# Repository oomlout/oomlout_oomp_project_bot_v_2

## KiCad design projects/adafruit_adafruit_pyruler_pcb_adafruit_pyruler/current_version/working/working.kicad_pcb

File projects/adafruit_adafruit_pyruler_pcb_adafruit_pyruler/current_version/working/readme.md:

# adafruit_pyruler_pcb
 
## summary 
* id: adafruit_adafruit_pyruler_pcb_adafruit_pyruler
* user: adafruit
* name: adafruit_pyruler_pcb
* board: adafruit_pyruler
* repo: https://github.com/adafruit/Adafruit-PyRuler-PCB

* src_file_repo_sch: 
* src_file_repo_sch_link: https://github.com/adafruit/Adafruit-PyRuler-PCB/tree/master/
* full details link: https://github.com/oomlout/oomlout_oomp_project_bot_v_2/tree/main/projects/adafruit_adafruit_pyruler_pcb_adafruit_pyruler/current_version/working  

## schematic  
  
[schematic (pdf)](working_schematic.pdf) 

## pcb  

[board (pdf)](working.pdf)  

## working_bom
| Id | Designator | Footprint | Quantity | Designation | Supplier and ref |  | None | 
| --- | --- | --- | --- | --- | --- | --- | --- | 
| 1 | @HOLE1,@HOLE0 |  | 2 |  |  |  | [''] | 
| 2 | E$18,E$21,E$17,E$20,E$22,E$19 | EDGE-INCHES-TENTH | 6 |  |  |  | [''] | 
| 3 | JP4,JP3 | 1X05_ROUND_70 | 2 |  |  |  | [''] | 
| 4 | E$8,E$11,E$7,E$6,E$12,E$15,E$9,E$5,E$13,E$1,E$3,E$2,E$14,E$10,E$4 | EDGE-MILLIMETERS | 15 |  |  |  | [''] | 
| 5 | C3,C2 | 0603-NO | 2 | 1uF |  |  | [''] | 
| 6 | U1 | SOT23-5 | 1 | AP2112K-3.3 |  |  | [''] | 
| 7 | R1,R2,R3 | 0603-NO | 3 | 2.2K |  |  | [''] | 
| 8 | U$8,U$9 | MOUNTINGHOLE_2.0_PLATED | 2 | MOUNTINGHOLE2.0 |  |  | [''] | 
| 9 | Q2 | BTN_KMR2_4.6X2.8 | 1 | reset |  |  | [''] | 
| 10 | LED1 | APA102_2020 | 1 | AP102-2020 |  |  | [''] | 
| 11 | U$6,U$1 | FIDUCIAL_1MM | 2 | FIDUCIAL_1MM |  |  | [''] | 
| 12 | D2,D3 | SOD-123FL | 2 | SCHOTTKY |  |  | [''] | 
| 13 | U$20 | TRINKET_M0_TOP | 1 |  |  |  | [''] | 
| 14 | C1,C8 | 0805-NO | 2 | 10uF |  |  | [''] | 
| 15 | CN1 | 4UCONN_20329_NARROW | 1 | 4U#20329 |  |  | [''] | 
| 16 | R7 | 0603-NO | 1 | 2M |  |  | [''] | 
| 17 | L4,PWR0 | CHIPLED_0603_NOOUTLINE | 2 | green |  |  | [''] | 
| 18 | IC3 | QFN32_5MM | 1 | ATSAMD21E |  |  | [''] | 
| 19 | L2,L0 | CHIPLED_0603_NOOUTLINE | 2 | red |  |  | [''] | 
| 20 | L1 | CHIPLED_0603_NOOUTLINE | 1 | yellow |  |  | [''] | 
| 21 | U$14 | PYRULER_TOP | 1 |  |  |  | [''] | 
| 22 | L3 | CHIPLED_0603_NOOUTLINE | 1 | blue |  |  | [''] | 
| 23 | R5,R6,R4 | 0603-NO | 3 | 10K |  |  | [''] | 
| 24 | E$57 | SO08 | 1 |  |  |  | [''] | 
| 25 | U$2 | PYRULER_BOTTOM | 1 |  |  |  | [''] | 
| 26 | E$25 | 0805 | 1 |  |  |  | [''] | 
| 27 | E$38 | CRYSTAL-SMD-2.5X2 | 1 |  |  |  | [''] | 
| 28 | E$27 | 1210 | 1 |  |  |  | [''] | 
| 29 | E$32 | SOT89 | 1 |  |  |  | [''] | 
| 30 | E$53 | LED-GUIDE | 1 |  |  |  | [''] | 
| 31 | U$7 | PCBFEAT-REV-040 | 1 |  |  |  | [''] | 
| 32 | E$16,E$63,E$60 | 0201 | 3 |  |  |  | [''] | 
| 33 | E$31 | SOT223 | 1 |  |  |  | [''] | 
| 34 | E$40 | XTAL-2X1.2 | 1 |  |  |  | [''] | 
| 35 | E$50 | NMOS-SYMB | 1 |  |  |  | [''] | 
| 36 | E$39 | HC49UP | 1 |  |  |  | [''] | 
| 37 | E$33 | SOT23-5 | 1 |  |  |  | [''] | 
| 38 | E$36 | CRYSTAL-SMD-5X3.2 | 1 |  |  |  | [''] | 
| 39 | E$24,E$62 | 0603 | 2 |  |  |  | [''] | 
| 40 | SWD0,SWC0 | B1,27 | 2 | TPB1,27 |  |  | [''] | 
| 41 | E$54 | NPN-SYMB | 1 |  |  |  | [''] | 
| 42 | E$35 | SC70 | 1 |  |  |  | [''] | 
| 43 | E$49 | SOD80C | 1 |  |  |  | [''] | 
| 44 | E$55 | QFN-24 | 1 |  |  |  | [''] | 
| 45 | E$52 | DIODE-SYMB | 1 |  |  |  | [''] | 
| 46 | E$34 | SOT23-3 | 1 |  |  |  | [''] | 
| 47 | E$43 | SMA-DIODE | 1 |  |  |  | [''] | 
| 48 | E$41 | MICROMELF-R | 1 |  |  |  | [''] | 
| 49 | E$37 | CRYSTAL-SMD-3.2X2.5 | 1 |  |  |  | [''] | 
| 50 | E$28 | 2010 | 1 |  |  |  | [''] | 
| 51 | E$58 | TQFP32-5MM | 1 |  |  |  | [''] | 
| 52 | E$51 | PMOS-SYMB | 1 |  |  |  | [''] | 
| 53 | E$61,E$23 | 0402 | 2 |  |  |  | [''] | 
| 54 | E$44 | SMB-DIODE | 1 |  |  |  | [''] | 
| 55 | E$45 | SMC | 1 |  |  |  | [''] | 
| 56 | E$59 | PNP-SYMB | 1 |  |  |  | [''] | 
| 57 | E$26 | 1206 | 1 |  |  |  | [''] | 
| 58 | E$47 | SOD-128 | 1 |  |  |  | [''] | 
| 59 | E$48 | SOD-323 | 1 |  |  |  | [''] | 
| 60 | E$56 | TSSOP16 | 1 |  |  |  | [''] | 
| 61 | E$42 | SC79_INFINEON | 1 |  |  |  | [''] | 

## bom_schematic
| Ref | Qnty | Value | Cmp name | Footprint | Description | Vendor | DNP | 
| --- | --- | --- | --- | --- | --- | --- | --- | 
| C1, C8 | 2 | 10uF | CAP_CERAMIC0805-NOOUTLINE | working:0805-NO |  |  |  | 
| C2, C3 | 2 | 1uF | CAP_CERAMIC0603_NO | working:0603-NO |  |  |  | 
| CN1 | 1 | 4U#20329 | USB_MICRO_NARROW | working:4UCONN_20329_NARROW |  |  |  | 
| D2, D3 | 2 | SCHOTTKY | DIODE_SOD-123FL | working:SOD-123FL |  |  |  | 
| IC3 | 1 | ATSAMD21E | ATSAMD21E | working:QFN32_5MM |  |  |  | 
| JP3, JP4 | 2 | HEADER-1X570MIL | HEADER-1X570MIL | working:1X05_ROUND_70 |  |  |  | 
| L0, L2 | 2 | red | LED0603_NOOUTLINE | working:CHIPLED_0603_NOOUTLINE |  |  |  | 
| L1 | 1 | yellow | LED0603_NOOUTLINE | working:CHIPLED_0603_NOOUTLINE |  |  |  | 
| L3 | 1 | blue | LED0603_NOOUTLINE | working:CHIPLED_0603_NOOUTLINE |  |  |  | 
| L4 | 1 | green | LED0603_NOOUTLINE | working:CHIPLED_0603_NOOUTLINE |  |  |  | 
| LED1 | 1 | AP102-2020 | APA1022020 | working:APA102_2020 |  |  |  | 
| PWR0 | 1 | green | LED0603_NOOUTLINE | working:CHIPLED_0603_NOOUTLINE |  |  |  | 
| Q2 | 1 | reset | SWITCH_TACT_SMT4.6X2.8 | working:BTN_KMR2_4.6X2.8 |  |  |  | 
| R1, R2, R3 | 3 | 2.2K | RESISTOR_0603_NOOUT | working:0603-NO |  |  |  | 
| R4, R5, R6 | 3 | 10K | RESISTOR_0603_NOOUT | working:0603-NO |  |  |  | 
| R7 | 1 | 2M | RESISTOR_0603_NOOUT | working:0603-NO |  |  |  | 
| SWC0 | 1 | TPB1,27 | TPB1,27 | working:B1,27 |  |  |  | 
| SWD0 | 1 | TPB1,27 | TPB1,27 | working:B1,27 |  |  |  | 
| U1 | 1 | AP2112K-3.3 | VREG_SOT23-5 | working:SOT23-5 |  |  |  | 
| U$1, U$6 | 2 | FIDUCIAL_1MM | FIDUCIAL_1MM | working:FIDUCIAL_1MM |  |  |  | 
| U$8, U$9 | 2 | MOUNTINGHOLE2.0 | MOUNTINGHOLE2.0 | working:MOUNTINGHOLE_2.0_PLATED |  |  |  | 

## mounting_holes
| x | y | package | value | ref | size | 
| --- | --- | --- | --- | --- | --- | 
| 0.0 | 0.0 | MOUNTINGHOLE_2.0_PLATED | MOUNTINGHOLE2.0 | U$8 | m3 | 
| 0.0 | 11.43 | MOUNTINGHOLE_2.0_PLATED | MOUNTINGHOLE2.0 | U$9 | m3 |

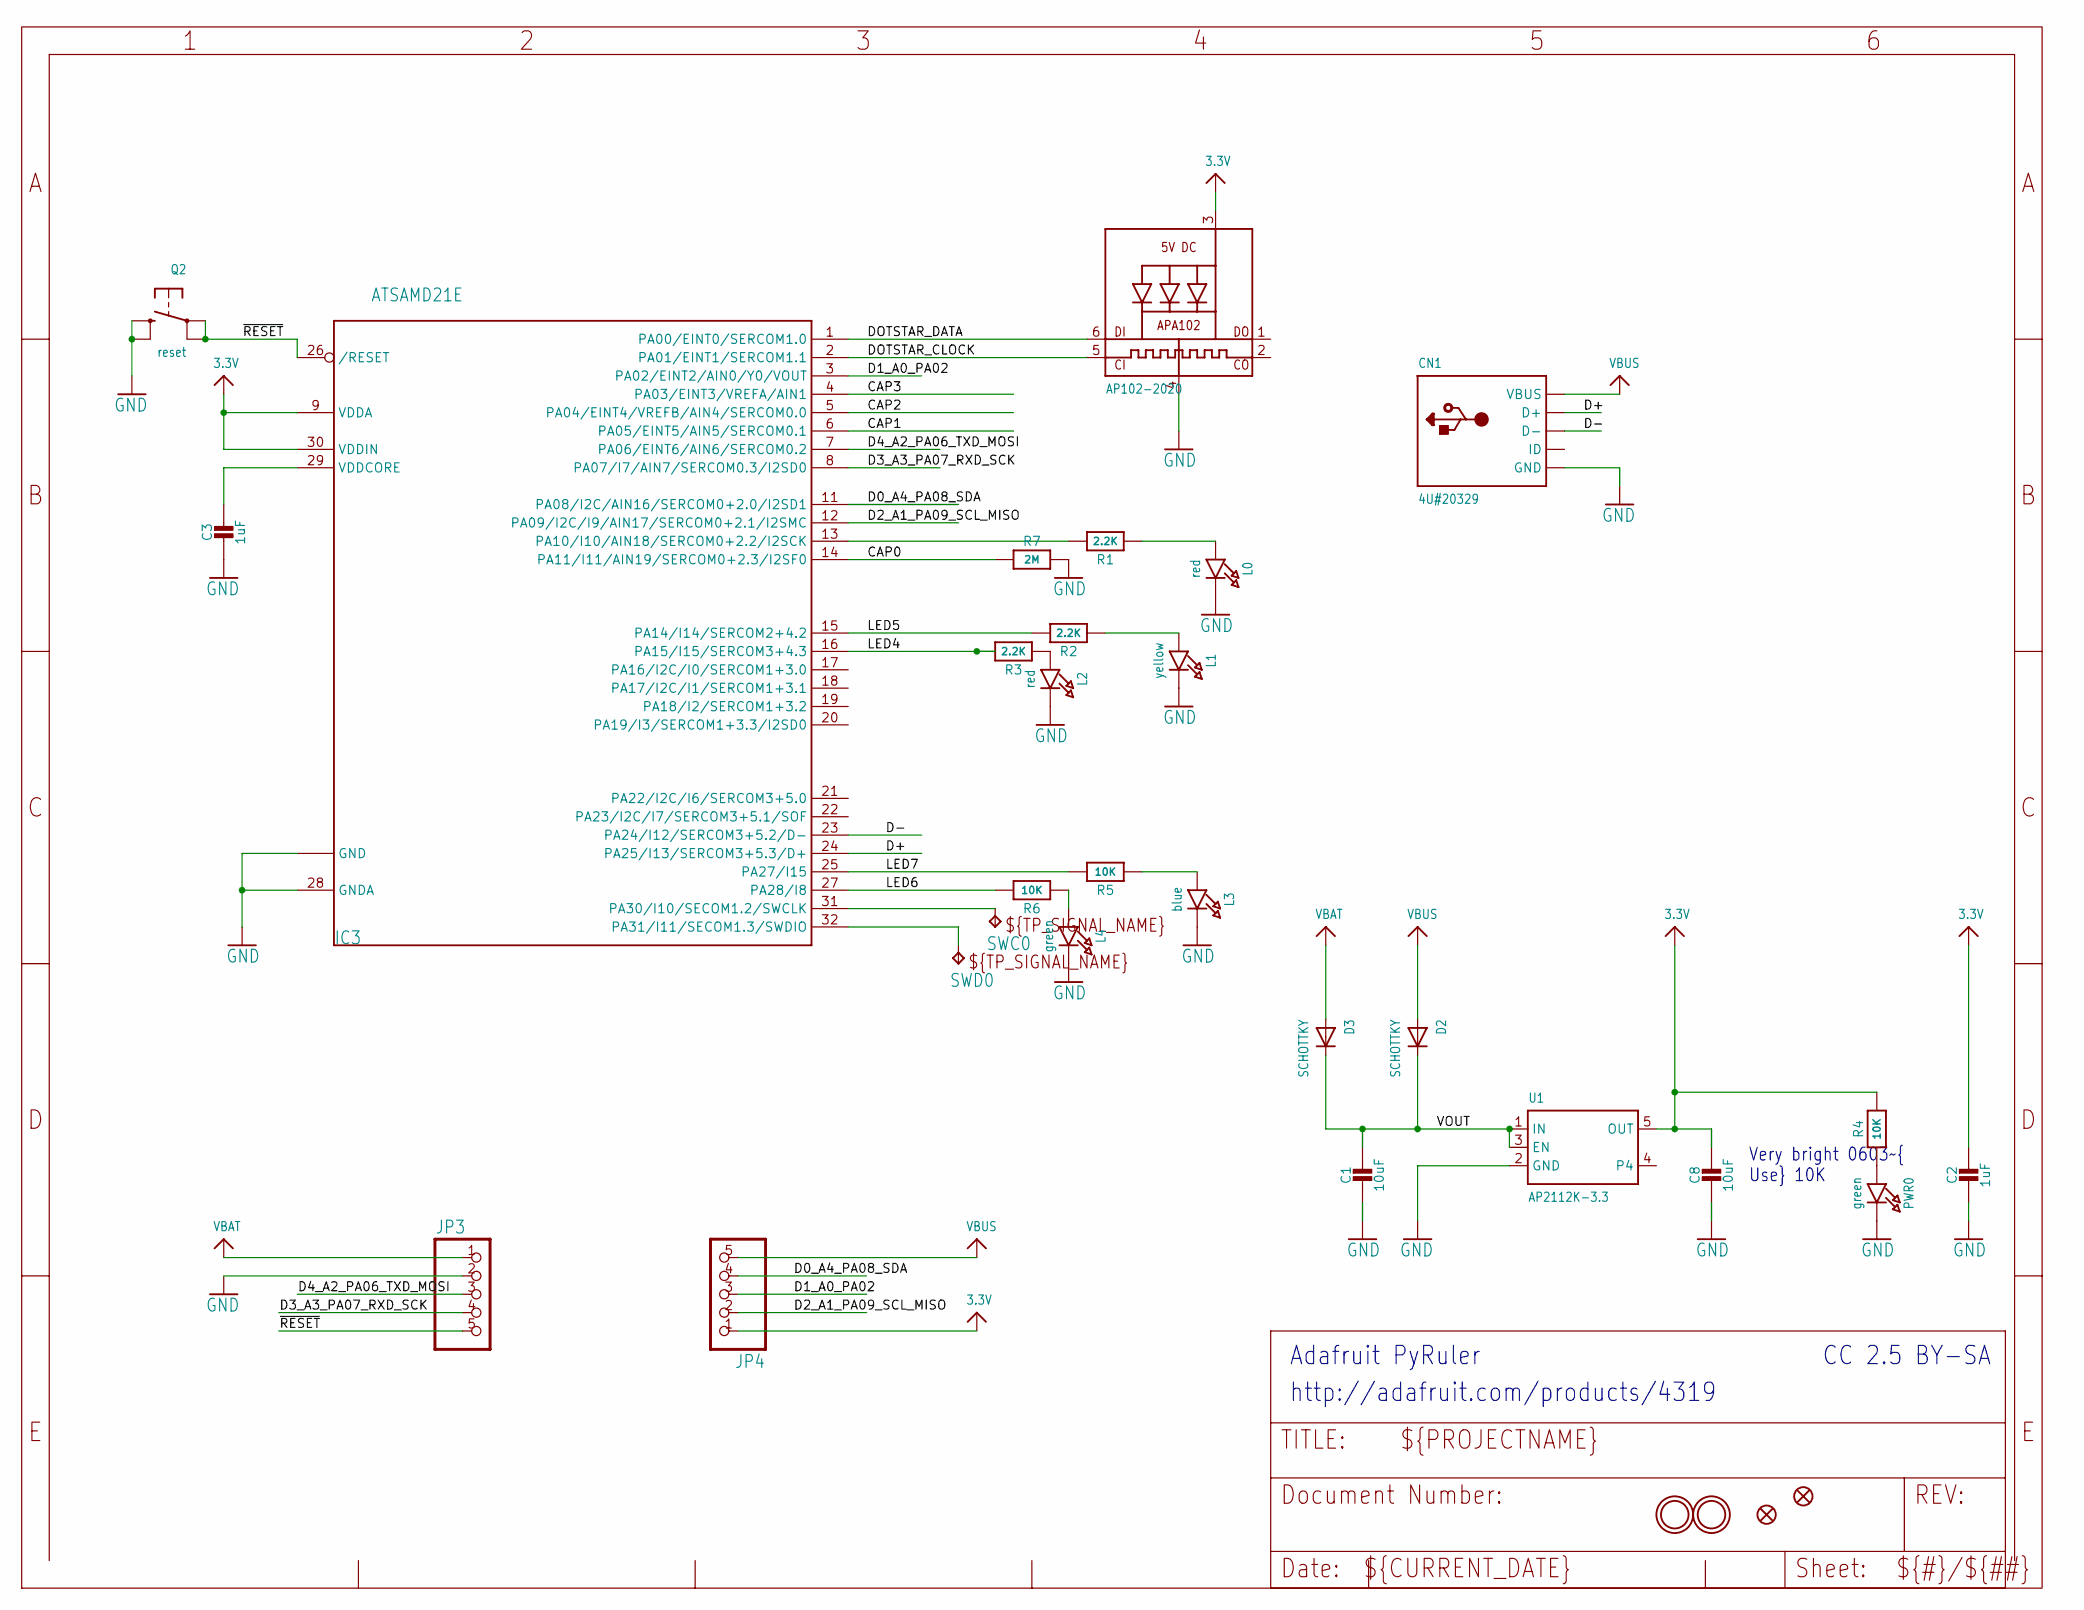
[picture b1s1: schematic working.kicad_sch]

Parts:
C1, C8: 10uF; 0805-NO
C2, C3: 1uF; 0603-NO
CN1: 4U#20329; 4UCONN_20329_NARROW
D2, D3: SCHOTTKY; SOD-123FL
IC3: ATSAMD21E; QFN32_5MM
JP3, JP4: HEADER-1X570MIL; 1X05_ROUND_70
L0, L2: red; CHIPLED_0603_NOOUTLINE
L1: yellow; CHIPLED_0603_NOOUTLINE
L3: blue; CHIPLED_0603_NOOUTLINE
L4: green; CHIPLED_0603_NOOUTLINE
LED1: AP102-2020; APA102_2020
PWR0: green; CHIPLED_0603_NOOUTLINE
Q2: reset; BTN_KMR2_4.6X2.8
R1, R2, R3: 2.2K; 0603-NO
R4, R5, R6: 10K; 0603-NO
R7: 2M; 0603-NO
SWC0: TPB1,27; B1,27
SWD0: TPB1,27; B1,27
U1: AP2112K-3.3; SOT23-5
U$1, U$6: FIDUCIAL_1MM
U$8, U$9: MOUNTINGHOLE2.0; MOUNTINGHOLE_2.0_PLATED

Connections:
3.3V: C2.1, C8.1, IC3.9 (VDDA), IC3.30 (VDDIN), JP4.1, LED1.3 (VDD), R4.2, U1.5 (OUT)
CAP0: IC3.14 (PA11/I11/AIN19/SERCOM0+2.3/I2SF0), R7.1
CAP1: IC3.6 (PA05/EINT5/AIN5/SERCOM0.1)
CAP2: IC3.5 (PA04/EINT4/VREFB/AIN4/SERCOM0.0)
CAP3: IC3.4 (PA03/EINT3/VREFA/AIN1)
D0_A4_PA08_SDA: IC3.11 (PA08/I2C/AIN16/SERCOM0+2.0/I2SD1), JP4.4
D1_A0_PA02: IC3.3 (PA02/EINT2/AIN0/Y0/VOUT), JP4.3
D2_A1_PA09_SCL_MISO: IC3.12 (PA09/I2C/I9/AIN17/SERCOM0+2.1/I2SMC), JP4.2
D3_A3_PA07_RXD_SCK: IC3.8 (PA07/I7/AIN7/SERCOM0.3/I2SD0), JP3.4
D4_A2_PA06_TXD_MOSI: IC3.7 (PA06/EINT6/AIN6/SERCOM0.2), JP3.3
D+: CN1.D+, IC3.24 (PA25/I13/SERCOM3+5.3/D+)
D-: CN1.D-, IC3.23 (PA24/I12/SERCOM3+5.2/D-)
DOTSTAR_CLOCK: IC3.2 (PA01/EINT1/SERCOM1.1), LED1.5 (CKI)
DOTSTAR_DATA: IC3.1 (PA00/EINT0/SERCOM1.0), LED1.6 (DI)
GND: C1.2, C2.2, C3.2, C8.2, CN1.BASE@1 (GND), CN1.BASE@2 (GND), CN1.GND, CN1.SPRT@1 (GND), CN1.SPRT@2 (GND), CN1.SPRT@3 (GND), CN1.SPRT@4 (GND), IC3.10 (GND), IC3.28 (GNDA), IC3.33 (GND), JP3.2, L0.C, L1.C, L2.C, L3.C, L4.C, LED1.4 (GND), PWR0.C, Q2.B (S), Q2.B' (S1), R7.2, U1.2 (GND)
LED: IC3.13 (PA10/I10/AIN18/SERCOM0+2.2/I2SCK), R1.2
LED4: IC3.16 (PA15/I15/SERCOM3+4.3), R3.2
LED5: IC3.15 (PA14/I14/SERCOM2+4.2), R2.2
LED6: IC3.27 (PA28/I8), R6.2
LED7: IC3.25 (PA27/I15), R5.2
unnamed: L0.A, R1.1
unnamed: IC3.31 (PA30/I10/SECOM1.2/SWCLK), SWC0.TP
unnamed: IC3.32 (PA31/I11/SECOM1.3/SWDIO), SWD0.TP
unnamed: PWR0.A, R4.1
unnamed: L1.A, R2.1
unnamed: L2.A, R3.1
unnamed: L4.A, R6.1
unnamed: L3.A, R5.1
VBAT: D3.A, JP3.1
VBUS: CN1.VBUS, D2.A, JP4.5
VDDCORE: C3.1, IC3.29 (VDDCORE)
VOUT: C1.1, D2.C, D3.C, U1.1 (IN), U1.3 (EN)
~RESET: IC3.26 (/RESET), JP3.5, Q2.A, Q2.A' (P1)

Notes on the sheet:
Adafruit PyRuler
http://adafruit.com/products/4319
Very bright 0603~{ Use} 10K
CC 2.5 BY-SA

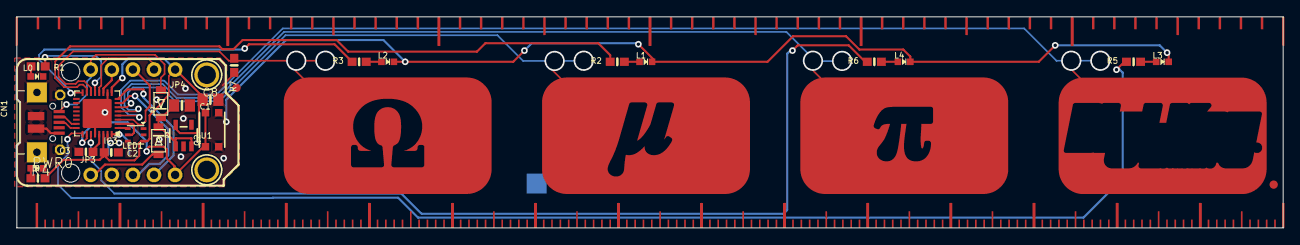
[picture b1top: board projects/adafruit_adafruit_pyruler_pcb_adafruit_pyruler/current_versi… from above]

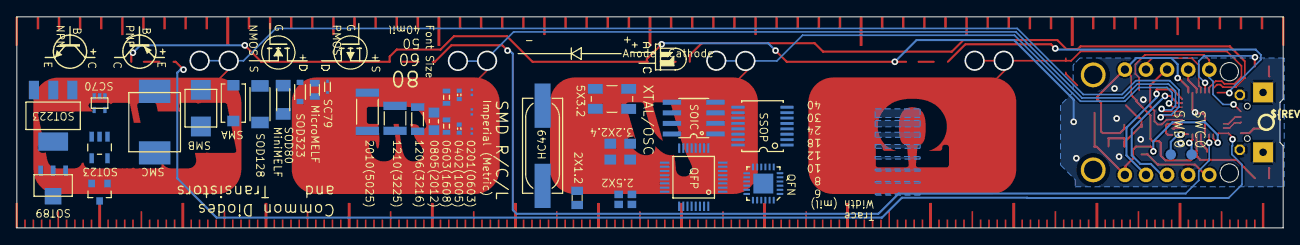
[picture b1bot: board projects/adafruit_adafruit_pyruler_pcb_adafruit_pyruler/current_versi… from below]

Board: 16 copper layers, 152.4 x 25.4 mm, 98 parts (43 on the bottom side), 30 nets.

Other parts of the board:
@HOLE0, @HOLE1: (no value)
E$1, E$2, E$3, E$4, E$5, E$6, E$7, E$8, E$9, E$10, E$11, E$12, E$13, E$14, E$15: EDGE-MILLIMETERS
E$16, E$60, E$63: 0201
E$17, E$18, E$19, E$20, E$21, E$22: EDGE-INCHES-TENTH
E$23, E$61: 0402
E$24, E$62: 0603
E$25: 0805
E$26: 1206
E$27: 1210
E$28: 2010
E$31: SOT223
E$32: SOT89
E$33: SOT23-5
E$34: SOT23-3
E$35: SC70
E$36: CRYSTAL-SMD-5X3.2
E$37: CRYSTAL-SMD-3.2X2.5
E$38: CRYSTAL-SMD-2.5X2
E$39: HC49UP
E$40: XTAL-2X1.2
E$41: MICROMELF-R
E$42: SC79_INFINEON
E$43: SMA-DIODE
E$44: SMB-DIODE
E$45: SMC
E$47: SOD-128
E$48: SOD-323
E$49: SOD80C
E$50: NMOS-SYMB
E$51: PMOS-SYMB
E$52: DIODE-SYMB
E$53: LED-GUIDE
E$54: NPN-SYMB
E$55: QFN-24
E$56: TSSOP16
E$57: SO08
E$58: TQFP32-5MM
E$59: PNP-SYMB
U$2: PYRULER_BOTTOM
U$7: PCBFEAT-REV-040
U$14: PYRULER_TOP
U$20: TRINKET_M0_TOP

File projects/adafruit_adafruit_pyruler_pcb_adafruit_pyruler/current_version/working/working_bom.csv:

"Id";"Designator";"Footprint";"Quantity";"Designation";"Supplier and ref";
1;"@HOLE1,@HOLE0";"";2;"";;;
2;"E$18,E$21,E$17,E$20,E$22,E$19";"EDGE-INCHES-TENTH";6;"";;;
3;"JP4,JP3";"1X05_ROUND_70";2;"";;;
4;"E$8,E$11,E$7,E$6,E$12,E$15,E$9,E$5,E$13,E$1,E$3,E$2,E$14,E$10,E$4";"EDGE-MILLIMETERS";15;"";;;
5;"C3,C2";"0603-NO";2;"1uF";;;
6;"U1";"SOT23-5";1;"AP2112K-3.3";;;
7;"R1,R2,R3";"0603-NO";3;"2.2K";;;
8;"U$8,U$9";"MOUNTINGHOLE_2.0_PLATED";2;"MOUNTINGHOLE2.0";;;
9;"Q2";"BTN_KMR2_4.6X2.8";1;"reset";;;
10;"LED1";"APA102_2020";1;"AP102-2020";;;
11;"U$6,U$1";"FIDUCIAL_1MM";2;"FIDUCIAL_1MM";;;
12;"D2,D3";"SOD-123FL";2;"SCHOTTKY";;;
13;"U$20";"TRINKET_M0_TOP";1;"";;;
14;"C1,C8";"0805-NO";2;"10uF";;;
15;"CN1";"4UCONN_20329_NARROW";1;"4U#20329";;;
16;"R7";"0603-NO";1;"2M";;;
17;"L4,PWR0";"CHIPLED_0603_NOOUTLINE";2;"green";;;
18;"IC3";"QFN32_5MM";1;"ATSAMD21E";;;
19;"L2,L0";"CHIPLED_0603_NOOUTLINE";2;"red";;;
20;"L1";"CHIPLED_0603_NOOUTLINE";1;"yellow";;;
21;"U$14";"PYRULER_TOP";1;"";;;
22;"L3";"CHIPLED_0603_NOOUTLINE";1;"blue";;;
23;"R5,R6,R4";"0603-NO";3;"10K";;;
24;"E$57";"SO08";1;"";;;
25;"U$2";"PYRULER_BOTTOM";1;"";;;
26;"E$25";"0805";1;"";;;
27;"E$38";"CRYSTAL-SMD-2.5X2";1;"";;;
28;"E$27";"1210";1;"";;;
29;"E$32";"SOT89";1;"";;;
30;"E$53";"LED-GUIDE";1;"";;;
31;"U$7";"PCBFEAT-REV-040";1;"";;;
32;"E$16,E$63,E$60";"0201";3;"";;;
33;"E$31";"SOT223";1;"";;;
34;"E$40";"XTAL-2X1.2";1;"";;;
35;"E$50";"NMOS-SYMB";1;"";;;
36;"E$39";"HC49UP";1;"";;;
37;"E$33";"SOT23-5";1;"";;;
38;"E$36";"CRYSTAL-SMD-5X3.2";1;"";;;
39;"E$24,E$62";"0603";2;"";;;
40;"SWD0,SWC0";"B1,27";2;"TPB1,27";;;
41;"E$54";"NPN-SYMB";1;"";;;
42;"E$35";"SC70";1;"";;;
43;"E$49";"SOD80C";1;"";;;
44;"E$55";"QFN-24";1;"";;;
45;"E$52";"DIODE-SYMB";1;"";;;
46;"E$34";"SOT23-3";1;"";;;
47;"E$43";"SMA-DIODE";1;"";;;
48;"E$41";"MICROMELF-R";1;"";;;
49;"E$37";"CRYSTAL-SMD-3.2X2.5";1;"";;;
50;"E$28";"2010";1;"";;;
51;"E$58";"TQFP32-5MM";1;"";;;
52;"E$51";"PMOS-SYMB";1;"";;;
53;"E$61,E$23";"0402";2;"";;;
54;"E$44";"SMB-DIODE";1;"";;;
55;"E$45";"SMC";1;"";;;
56;"E$59";"PNP-SYMB";1;"";;;
57;"E$26";"1206";1;"";;;
58;"E$47";"SOD-128";1;"";;;
59;"E$48";"SOD-323";1;"";;;
60;"E$56";"TSSOP16";1;"";;;
61;"E$42";"SC79_INFINEON";1;"";;;

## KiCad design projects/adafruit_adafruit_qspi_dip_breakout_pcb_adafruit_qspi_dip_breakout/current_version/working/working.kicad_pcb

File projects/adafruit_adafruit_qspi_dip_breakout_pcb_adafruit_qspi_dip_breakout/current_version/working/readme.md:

# adafruit_qspi_dip_breakout_pcb
 
## summary 
* id: adafruit_adafruit_qspi_dip_breakout_pcb_adafruit_qspi_dip_breakout
* user: adafruit
* name: adafruit_qspi_dip_breakout_pcb
* board: adafruit_qspi_dip_breakout
* repo: https://github.com/adafruit/Adafruit-QSPI-DIP-Breakout-PCB

* src_file_repo_sch: 
* src_file_repo_sch_link: https://github.com/adafruit/Adafruit-QSPI-DIP-Breakout-PCB/tree/main/
* full details link: https://github.com/oomlout/oomlout_oomp_project_bot_v_2/tree/main/projects/adafruit_adafruit_qspi_dip_breakout_pcb_adafruit_qspi_dip_breakout/current_version/working  

## schematic  
  
[schematic (pdf)](working_schematic.pdf) 

## pcb  

[board (pdf)](working.pdf)  

## working_bom
| Id | Designator | Footprint | Quantity | Designation | Supplier and ref |  | None | 
| --- | --- | --- | --- | --- | --- | --- | --- | 
| 1 | JP3,JP2 | 1X04_ROUND_76 | 2 |  |  |  | [''] | 
| 2 | FID1 | FIDUCIAL_1MM | 1 | FIDUCIAL_1MM |  |  | [''] | 
| 3 | U1 | SOIC8_208MIL | 1 | GENERIC QSPI |  |  | [''] | 
| 4 | U$4 | ADAFRUIT_2.5MM | 1 |  |  |  | [''] | 

## bom_schematic
| Ref | Qnty | Value | Cmp name | Footprint | Description | Vendor | DNP | 
| --- | --- | --- | --- | --- | --- | --- | --- | 
| FID1 | 1 | FIDUCIAL_1MM | FIDUCIAL_1MM | working:FIDUCIAL_1MM |  |  |  | 
| JP2, JP3 | 2 | HEADER-1X476MIL | HEADER-1X476MIL | working:1X04_ROUND_76 |  |  |  | 
| U1 | 1 | GENERIC QSPI | SPIFLASH_8PIN208MIL | working:SOIC8_208MIL |  |  |  |

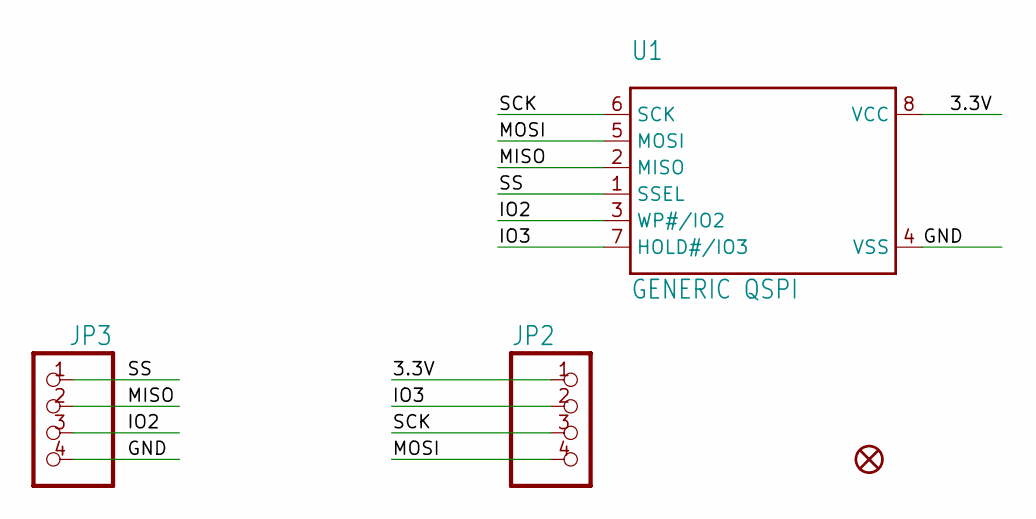
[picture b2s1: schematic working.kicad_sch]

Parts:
FID1: FIDUCIAL_1MM
JP2, JP3: HEADER-1X476MIL; 1X04_ROUND_76
U1: GENERIC QSPI; SOIC8_208MIL

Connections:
3.3V: JP2.1, U1.8 (VCC)
GND: JP3.4, U1.4 (VSS)
IO2: JP3.3, U1.3 (WP#/IO2)
IO3: JP2.2, U1.7 (HOLD#/IO3)
MISO: JP3.2, U1.2 (MISO)
MOSI: JP2.4, U1.5 (MOSI)
SCK: JP2.3, U1.6 (SCK)
SS: JP3.1, U1.1 (SSEL)

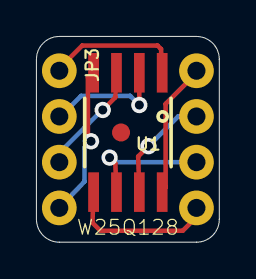
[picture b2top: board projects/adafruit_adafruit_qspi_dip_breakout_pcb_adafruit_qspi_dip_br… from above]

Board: 2 copper layers, 10.2 x 11.4 mm, 5 parts (1 on the bottom side), 8 nets.

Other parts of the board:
U$4: ADAFRUIT_2.5MM

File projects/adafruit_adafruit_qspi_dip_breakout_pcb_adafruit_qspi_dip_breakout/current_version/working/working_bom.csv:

"Id";"Designator";"Footprint";"Quantity";"Designation";"Supplier and ref";
1;"JP3,JP2";"1X04_ROUND_76";2;"";;;
2;"FID1";"FIDUCIAL_1MM";1;"FIDUCIAL_1MM";;;
3;"U1";"SOIC8_208MIL";1;"GENERIC QSPI";;;
4;"U$4";"ADAFRUIT_2.5MM";1;"";;;

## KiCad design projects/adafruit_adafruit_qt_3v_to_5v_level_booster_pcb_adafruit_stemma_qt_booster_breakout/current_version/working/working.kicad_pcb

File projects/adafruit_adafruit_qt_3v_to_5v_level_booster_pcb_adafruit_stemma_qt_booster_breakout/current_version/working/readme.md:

# adafruit_qt_3v_to_5v_level_booster_pcb
 
## summary 
* id: adafruit_adafruit_qt_3v_to_5v_level_booster_pcb_adafruit_stemma_qt_booster_breakout
* user: adafruit
* name: adafruit_qt_3v_to_5v_level_booster_pcb
* board: adafruit_stemma_qt_booster_breakout
* repo: https://github.com/adafruit/Adafruit-QT-3V-to-5V-Level-Booster-PCB

* src_file_repo_sch: 
* src_file_repo_sch_link: https://github.com/adafruit/Adafruit-QT-3V-to-5V-Level-Booster-PCB/tree/main/
* full details link: https://github.com/oomlout/oomlout_oomp_project_bot_v_2/tree/main/projects/adafruit_adafruit_qt_3v_to_5v_level_booster_pcb_adafruit_stemma_qt_booster_breakout/current_version/working  

## schematic  
  
[schematic (pdf)](working_schematic.pdf) 

## pcb  

[board (pdf)](working.pdf)  

## working_bom
| Id | Designator | Footprint | Quantity | Designation | Supplier and ref |  | None | 
| --- | --- | --- | --- | --- | --- | --- | --- | 
| 1 | IC1 | SOT23-6 | 1 | AP3602/RT9361 |  |  | [''] | 
| 2 | D1 | CHIPLED_0603_NOOUTLINE | 1 | GREEN |  |  | [''] | 
| 3 | PLABEL12 | PLABEL12 | 1 |  |  |  | [''] | 
| 4 | C4,C5 | 0805-NO | 2 | 10uF |  |  | [''] | 
| 5 | Q2 | SOT363 | 1 | BSS138 |  |  | [''] | 
| 6 | PLABEL0 | PLABEL0 | 1 |  |  |  | [''] | 
| 7 | PLABEL5 | PLABEL5 | 1 |  |  |  | [''] | 
| 8 | C1 | 0603-NO | 1 | 0.1uF |  |  | [''] | 
| 9 | PLABEL7 | PLABEL7 | 1 |  |  |  | [''] | 
| 10 | PLABEL3 | PLABEL3 | 1 |  |  |  | [''] | 
| 11 | CONN3,CONN4 | JST_SH4 | 2 | STEMMA_I2C_QT |  |  | [''] | 
| 12 | PLABEL10 | PLABEL10 | 1 |  |  |  | [''] | 
| 13 | C6 | 0805-NO | 1 | 1uF |  |  | [''] | 
| 14 | U$1,U$21,U$17,U$19 | MOUNTINGHOLE_2.5_PLATED | 4 | MOUNTINGHOLE2.5 |  |  | [''] | 
| 15 | JP2,JP3 | 1X05_ROUND_76 | 2 |  |  |  | [''] | 
| 16 | PLABEL1 | PLABEL1 | 1 |  |  |  | [''] | 
| 17 | R3 | RESPACK_4X0603 | 1 | 10K Pack |  |  | [''] | 
| 18 | R1 | 0603-NO | 1 | 10K |  |  | [''] | 
| 19 | PLABEL2 | PLABEL2 | 1 |  |  |  | [''] | 
| 20 | PLABEL6 | PLABEL6 | 1 |  |  |  | [''] | 
| 21 | FID3,FID4 | FIDUCIAL_1MM | 2 | FIDUCIAL_1MM |  |  | [''] | 
| 22 | PLABEL8 | PLABEL8 | 1 |  |  |  | [''] | 
| 23 | PLABEL9 | PLABEL9 | 1 |  |  |  | [''] | 
| 24 | PLABEL11 | PLABEL11 | 1 |  |  |  | [''] | 
| 25 | PLABEL4 | PLABEL4 | 1 |  |  |  | [''] | 
| 26 | SJ1 | SOLDERJUMPER_CLOSEDWIRE | 1 |  |  |  | [''] | 
| 27 | U$30,U$31 | STEMMAQT | 2 |  |  |  | [''] | 
| 28 | U$2 | ADAFRUIT_3.5MM | 1 |  |  |  | [''] | 
| 29 | SJ2 | SOLDERJUMPER_2WAY_OPEN_NOPASTE | 1 |  |  |  | [''] | 
| 30 | PLABEL14 | PLABEL14 | 1 |  |  |  | [''] | 
| 31 | PLABEL13 | PLABEL13 | 1 |  |  |  | [''] | 
| 32 | U$25 | PCBFEAT-REV-040 | 1 |  |  |  | [''] | 

## bom_schematic
| Ref | Qnty | Value | Cmp name | Footprint | Description | Vendor | DNP | 
| --- | --- | --- | --- | --- | --- | --- | --- | 
| C1 | 1 | 0.1uF | CAP_CERAMIC0603_NO | working:0603-NO |  |  |  | 
| C4, C5 | 2 | 10uF | CAP_CERAMIC0805-NOOUTLINE | working:0805-NO |  |  |  | 
| C6 | 1 | 1uF | CAP_CERAMIC0805-NOOUTLINE | working:0805-NO |  |  |  | 
| CONN3, CONN4 | 2 | STEMMA_I2C_QT | STEMMA_I2C_QT | working:JST_SH4 |  |  |  | 
| D1 | 1 | GREEN | LED0603_NOOUTLINE | working:CHIPLED_0603_NOOUTLINE |  |  |  | 
| FID3, FID4 | 2 | FIDUCIAL_1MM | FIDUCIAL_1MM | working:FIDUCIAL_1MM |  |  |  | 
| IC1 | 1 | AP3602 | AP3602 | working:SOT23-6 |  |  |  | 
| JP2, JP3 | 2 | HEADER-1X576MIL | HEADER-1X576MIL | working:1X05_ROUND_76 |  |  |  | 
| Q2 | 1 | BSS138 | MOSFET-N_DUAL | working:SOT363 |  |  |  | 
| R1 | 1 | 10K | RESISTOR_0603_NOOUT | working:0603-NO |  |  |  | 
| R3 | 1 | 10K Pack | RESISTOR_4PACK | working:RESPACK_4X0603 |  |  |  | 
| SJ1 | 1 | SOLDERJUMPERCLOSED | SOLDERJUMPERCLOSED | working:SOLDERJUMPER_CLOSEDWIRE |  |  |  | 
| SJ2 | 1 | SOLDERJUMPER_2WAY | SOLDERJUMPER_2WAY | working:SOLDERJUMPER_2WAY_OPEN_NOPASTE |  |  |  | 
| U$1, U$17, U$19, U$21 | 4 | MOUNTINGHOLE2.5 | MOUNTINGHOLE2.5 | working:MOUNTINGHOLE_2.5_PLATED |  |  |  | 

## mounting_holes
| x | y | package | value | ref | size | 
| --- | --- | --- | --- | --- | --- | 
| 20.32 | 0.0 | MOUNTINGHOLE_2.5_PLATED | MOUNTINGHOLE2.5 | U$1 | m3 | 
| 0.0 | 0.0 | MOUNTINGHOLE_2.5_PLATED | MOUNTINGHOLE2.5 | U$17 | m3 | 
| 20.32 | 12.7 | MOUNTINGHOLE_2.5_PLATED | MOUNTINGHOLE2.5 | U$19 | m3 | 
| 0.0 | 12.7 | MOUNTINGHOLE_2.5_PLATED | MOUNTINGHOLE2.5 | U$21 | m3 |

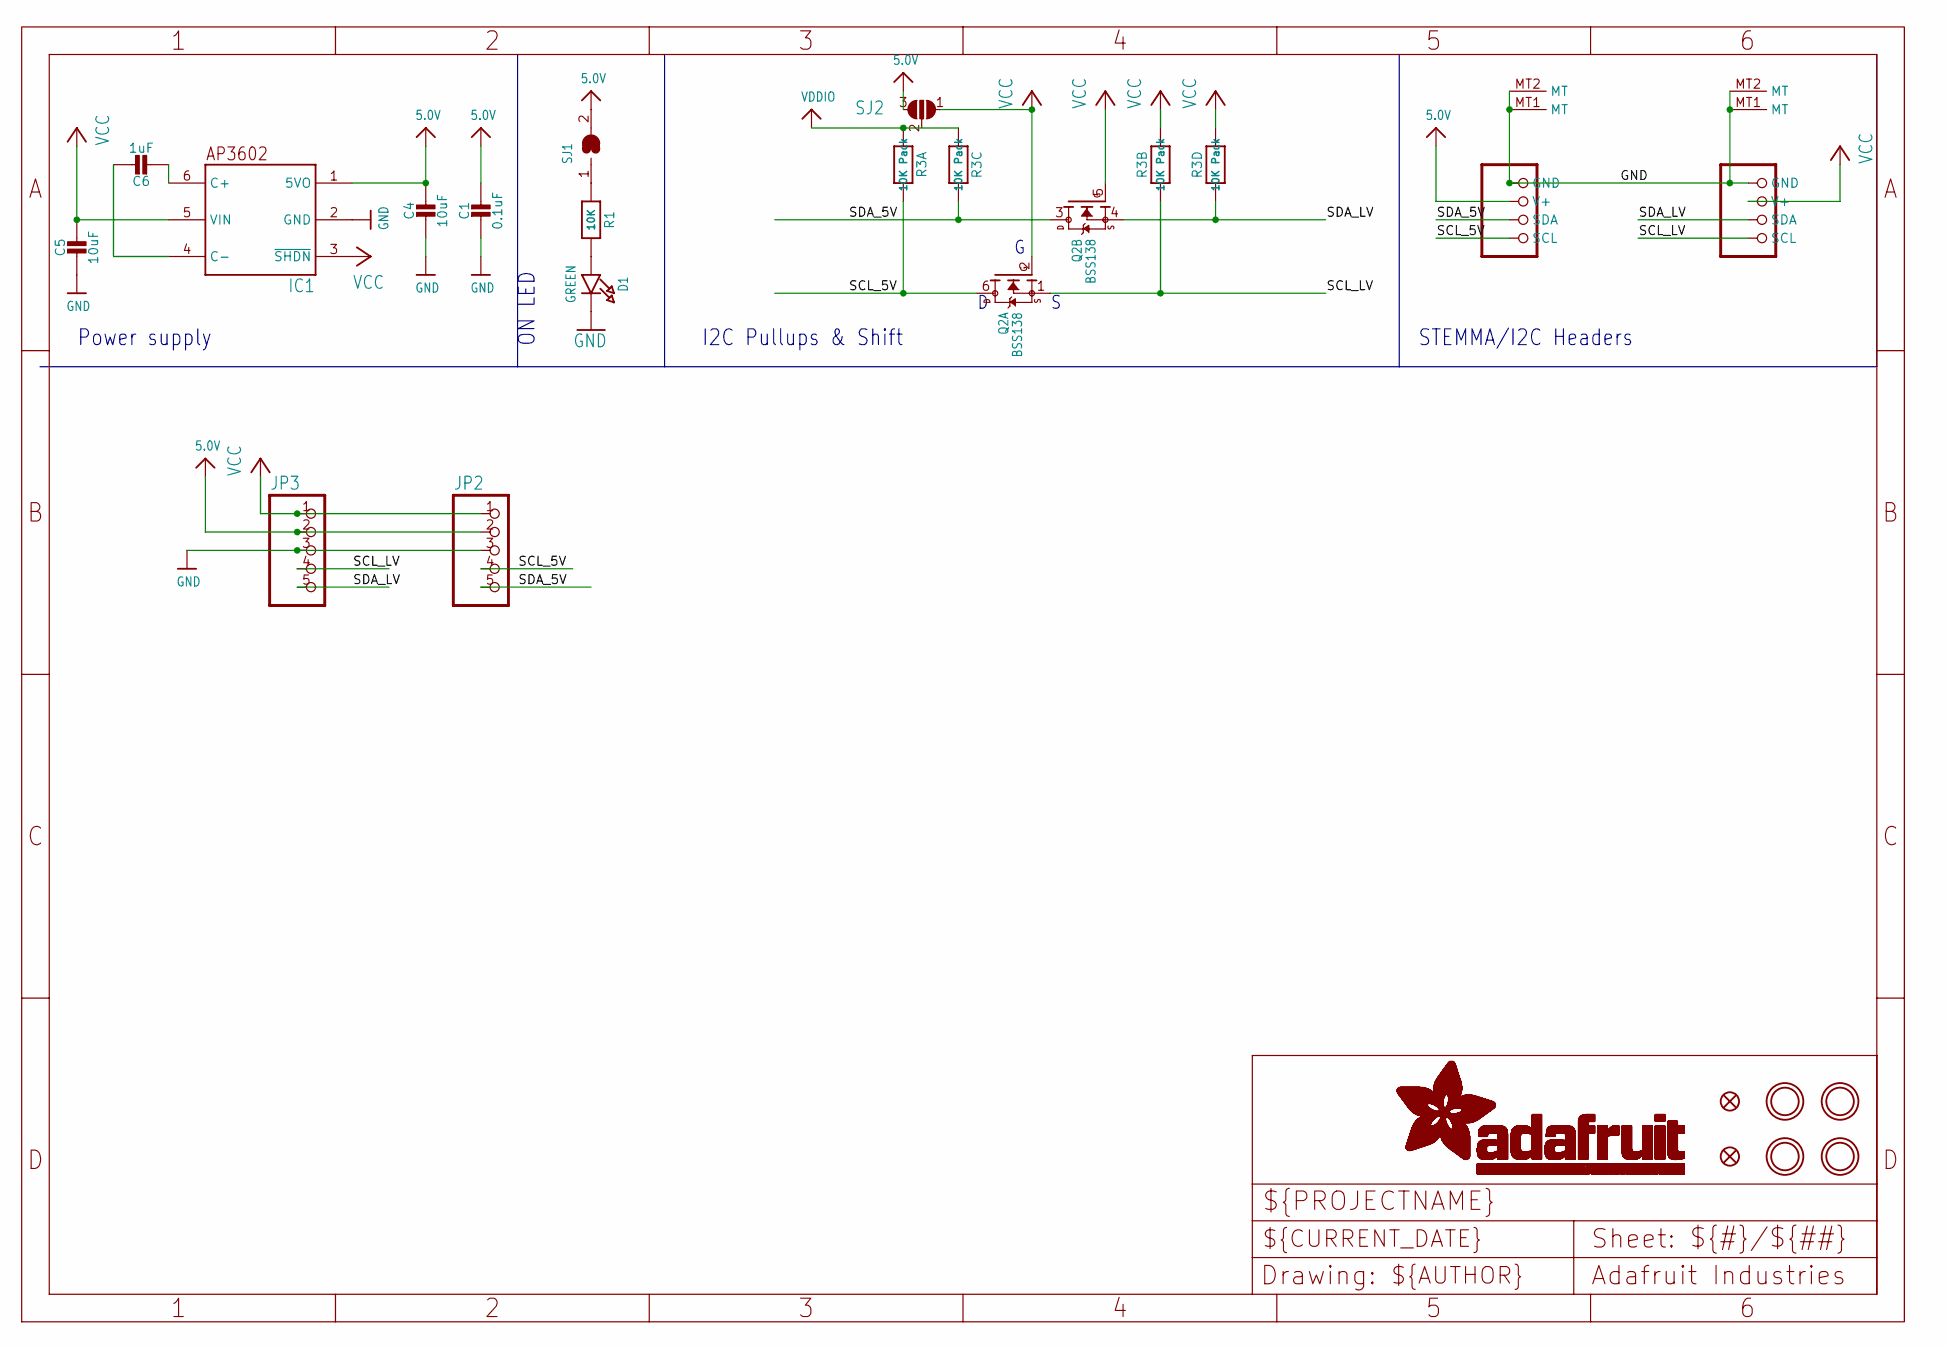
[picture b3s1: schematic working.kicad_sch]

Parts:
C1: 0.1uF; 0603-NO
C4, C5: 10uF; 0805-NO
C6: 1uF; 0805-NO
CONN3, CONN4: STEMMA_I2C_QT; JST_SH4
D1: GREEN; CHIPLED_0603_NOOUTLINE
FID3, FID4: FIDUCIAL_1MM
IC1: AP3602; SOT23-6
JP2, JP3: HEADER-1X576MIL; 1X05_ROUND_76
Q2: BSS138; SOT363
R1: 10K; 0603-NO
R3: 10K Pack; RESPACK_4X0603
SJ1: SOLDERJUMPERCLOSED; SOLDERJUMPER_CLOSEDWIRE
SJ2: SOLDERJUMPER_2WAY; SOLDERJUMPER_2WAY_OPEN_NOPASTE
U$1, U$17, U$19, U$21: MOUNTINGHOLE2.5; MOUNTINGHOLE_2.5_PLATED

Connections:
5.0V: C1.1, C4.1, CONN3.2 (V+), IC1.1 (5VO), JP2.2, JP3.2, SJ1.2, SJ2.3
GND: C1.2, C4.2, C5.2, CONN3.1 (GND), CONN3.MT1 (MT), CONN3.MT2 (MT), CONN4.1 (GND), CONN4.MT1 (MT), CONN4.MT2 (MT), D1.C, IC1.2 (GND), JP2.3, JP3.3
unnamed: D1.A, R1.2
unnamed: R1.1, SJ1.1
unnamed: C6.2, IC1.6 (C+)
unnamed: C6.1, IC1.4 (C-)
SCL_5V: CONN3.4 (SCL), JP2.4, Q2.6 (D), R3.8 (2)
SCL_LV: CONN4.4 (SCL), JP3.4, Q2.1 (S), R3.7 (2)
SDA_5V: CONN3.3 (SDA), JP2.5, Q2.3 (D), R3.6 (2)
SDA_LV: CONN4.3 (SDA), JP3.5, Q2.4 (S), R3.5 (2)
VCC: C5.1, CONN4.2 (V+), IC1.3 (~SHDN), IC1.5 (VIN), JP2.1, JP3.1, Q2.2 (G), Q2.5 (G), R3.2 (1), R3.4 (1), SJ2.1
VDDIO: R3.1, R3.3 (1), SJ2.2

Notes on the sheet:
STEMMA/I2C Headers
ON LED
Power supply
I2C Pullups & Shift

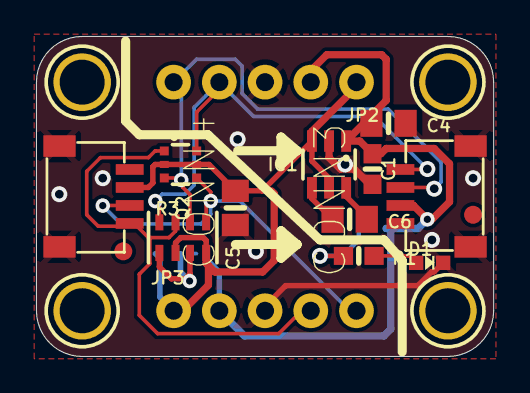
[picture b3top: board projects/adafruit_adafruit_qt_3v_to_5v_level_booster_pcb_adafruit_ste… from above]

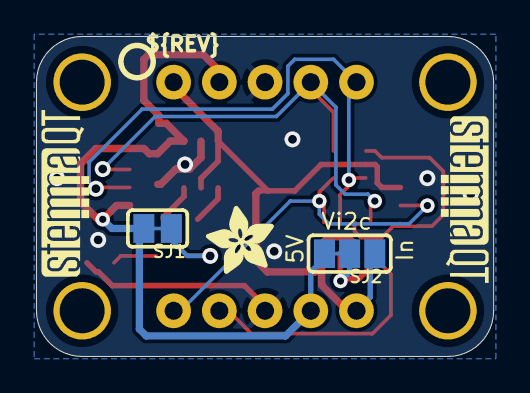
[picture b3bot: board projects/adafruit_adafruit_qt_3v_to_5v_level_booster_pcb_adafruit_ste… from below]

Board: 2 copper layers, 25.4 x 17.8 mm, 40 parts (8 on the bottom side), 12 nets.

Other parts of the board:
PLABEL0: PLABEL0
PLABEL1: PLABEL1
PLABEL2: PLABEL2
PLABEL3: PLABEL3
PLABEL4: PLABEL4
PLABEL5: PLABEL5
PLABEL6: PLABEL6
PLABEL7: PLABEL7
PLABEL8: PLABEL8
PLABEL9: PLABEL9
PLABEL10: PLABEL10
PLABEL11: PLABEL11
PLABEL12: PLABEL12
PLABEL13: PLABEL13
PLABEL14: PLABEL14
U$2: ADAFRUIT_3.5MM
U$25: PCBFEAT-REV-040
U$30, U$31: STEMMAQT

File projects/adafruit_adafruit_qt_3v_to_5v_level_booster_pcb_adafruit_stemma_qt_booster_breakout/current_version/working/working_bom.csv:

"Id";"Designator";"Footprint";"Quantity";"Designation";"Supplier and ref";
1;"IC1";"SOT23-6";1;"AP3602/RT9361";;;
2;"D1";"CHIPLED_0603_NOOUTLINE";1;"GREEN";;;
3;"PLABEL12";"PLABEL12";1;"";;;
4;"C4,C5";"0805-NO";2;"10uF";;;
5;"Q2";"SOT363";1;"BSS138";;;
6;"PLABEL0";"PLABEL0";1;"";;;
7;"PLABEL5";"PLABEL5";1;"";;;
8;"C1";"0603-NO";1;"0.1uF";;;
9;"PLABEL7";"PLABEL7";1;"";;;
10;"PLABEL3";"PLABEL3";1;"";;;
11;"CONN3,CONN4";"JST_SH4";2;"STEMMA_I2C_QT";;;
12;"PLABEL10";"PLABEL10";1;"";;;
13;"C6";"0805-NO";1;"1uF";;;
14;"U$1,U$21,U$17,U$19";"MOUNTINGHOLE_2.5_PLATED";4;"MOUNTINGHOLE2.5";;;
15;"JP2,JP3";"1X05_ROUND_76";2;"";;;
16;"PLABEL1";"PLABEL1";1;"";;;
17;"R3";"RESPACK_4X0603";1;"10K Pack";;;
18;"R1";"0603-NO";1;"10K";;;
19;"PLABEL2";"PLABEL2";1;"";;;
20;"PLABEL6";"PLABEL6";1;"";;;
21;"FID3,FID4";"FIDUCIAL_1MM";2;"FIDUCIAL_1MM";;;
22;"PLABEL8";"PLABEL8";1;"";;;
23;"PLABEL9";"PLABEL9";1;"";;;
24;"PLABEL11";"PLABEL11";1;"";;;
25;"PLABEL4";"PLABEL4";1;"";;;
26;"SJ1";"SOLDERJUMPER_CLOSEDWIRE";1;"";;;
27;"U$30,U$31";"STEMMAQT";2;"";;;
28;"U$2";"ADAFRUIT_3.5MM";1;"";;;
29;"SJ2";"SOLDERJUMPER_2WAY_OPEN_NOPASTE";1;"";;;
30;"PLABEL14";"PLABEL14";1;"";;;
31;"PLABEL13";"PLABEL13";1;"";;;
32;"U$25";"PCBFEAT-REV-040";1;"";;;
